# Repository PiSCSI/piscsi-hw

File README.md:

# piscsi-hw
Hardware Repository for PiSCSI

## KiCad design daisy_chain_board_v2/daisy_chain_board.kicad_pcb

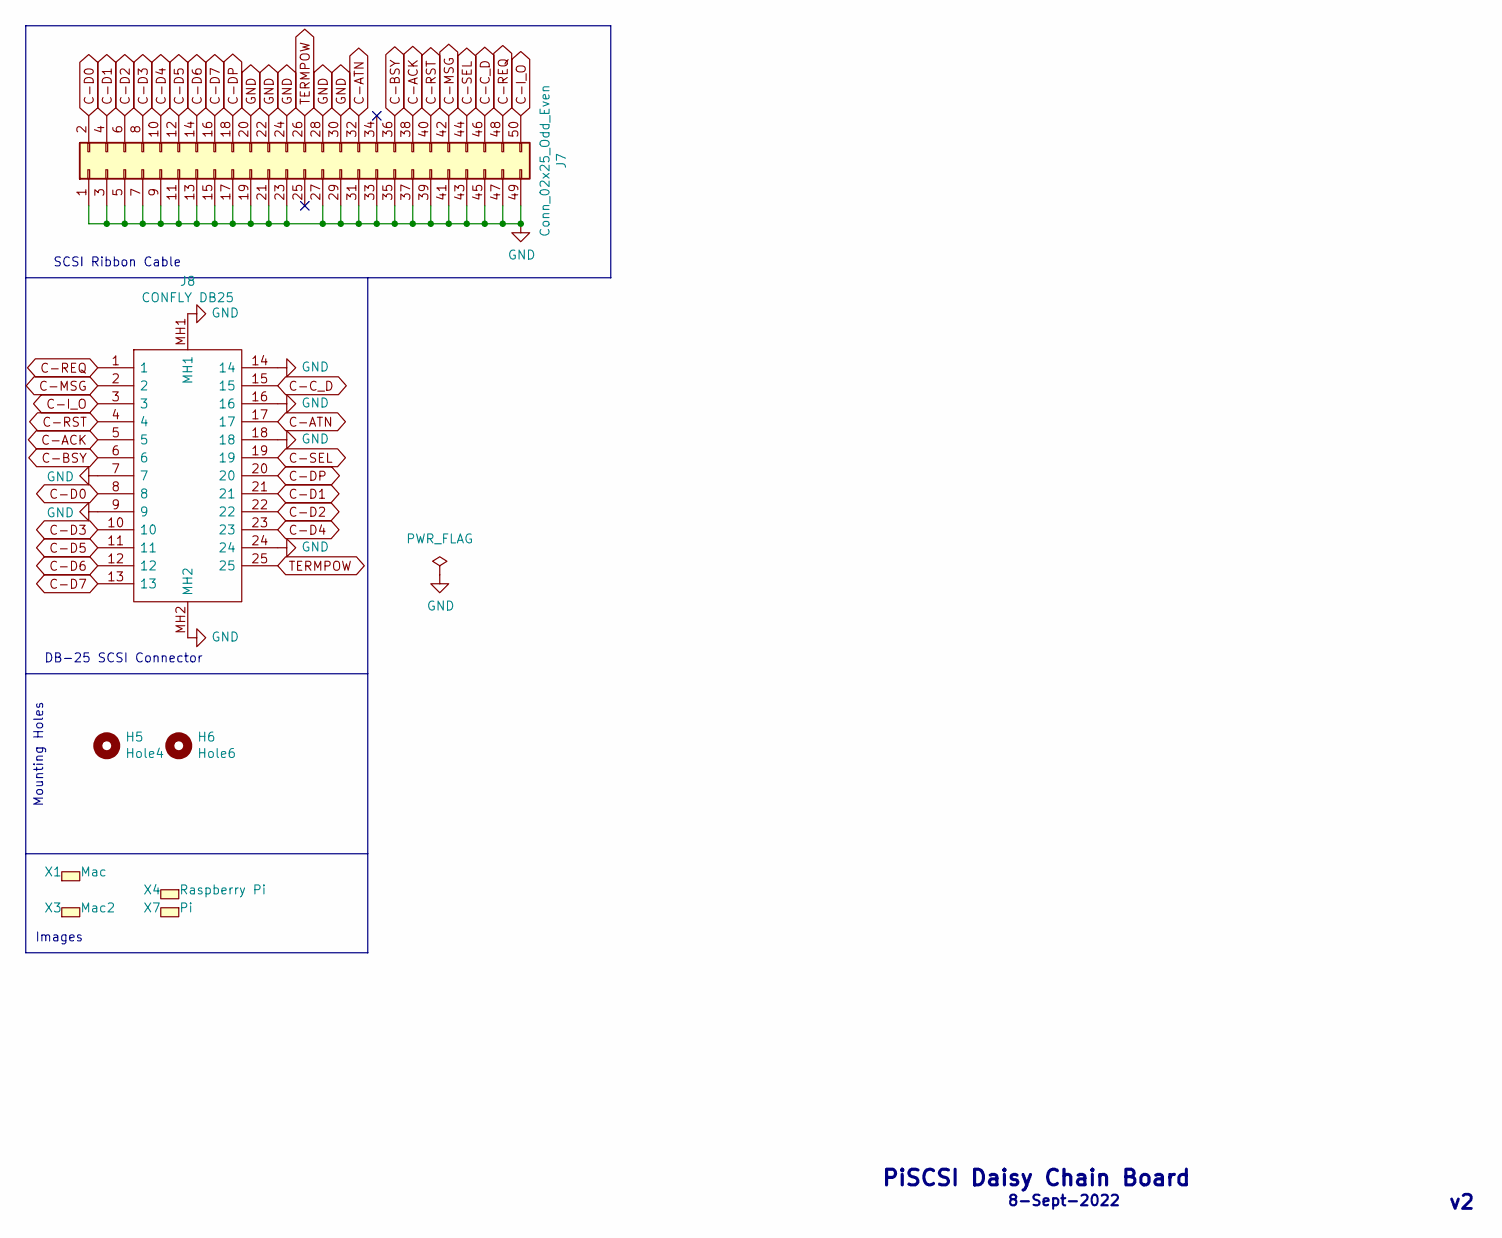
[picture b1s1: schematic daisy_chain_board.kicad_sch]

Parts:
H5: Hole4; MountingHole_2.7mm
H6: Hole6; MountingHole_2.7mm
J7: Conn_02x25_Odd_Even; PinHeader_2x25_P2.54mm_Vertical; LCSC C40024
J8: CONFLY DB25; L717SDB25PA4CH4F; Mouser Part Number 523-L717SDB25PA4CH4F
X1: Mac; mac_happy_small
X3: Mac2; mac_happy_small
X4: Raspberry Pi; pi_logo
X7: Pi; pi_logo

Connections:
C-ACK: J7.38, J8.5
C-ATN: J7.32, J8.17
C-BSY: J7.36, J8.6
C-C_D: J7.46, J8.15
C-D0: J7.2, J8.8
C-D1: J7.4, J8.21
C-D2: J7.6, J8.22
C-D3: J7.8, J8.10
C-D4: J7.10, J8.23
C-D5: J7.12, J8.11
C-D6: J7.14, J8.12
C-D7: J7.16, J8.13
C-DP: J7.18, J8.20
C-I_O: J7.50, J8.3
C-MSG: J7.42, J8.2
C-REQ: J7.48, J8.1
C-RST: J7.40, J8.4
C-SEL: J7.44, J8.19
GND: J7.1, J7.3, J7.5, J7.7, J7.9, J7.11, J7.13, J7.15, J7.17, J7.19, J7.20, J7.21, J7.22, J7.23, J7.24, J7.27, J7.28, J7.29, J7.30, J7.31, J7.33, J7.35, J7.37, J7.39, J7.41, J7.43, J7.45, J7.47, J7.49, J8.7, J8.9, J8.14, J8.16, J8.18, J8.24, J8.MH1, J8.MH2
TERMPOW: J7.26, J8.25

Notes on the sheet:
DB-25 SCSI Connector
Images
8-Sept-2022
PiSCSI Daisy Chain Board
Mounting Holes
SCSI Ribbon Cable

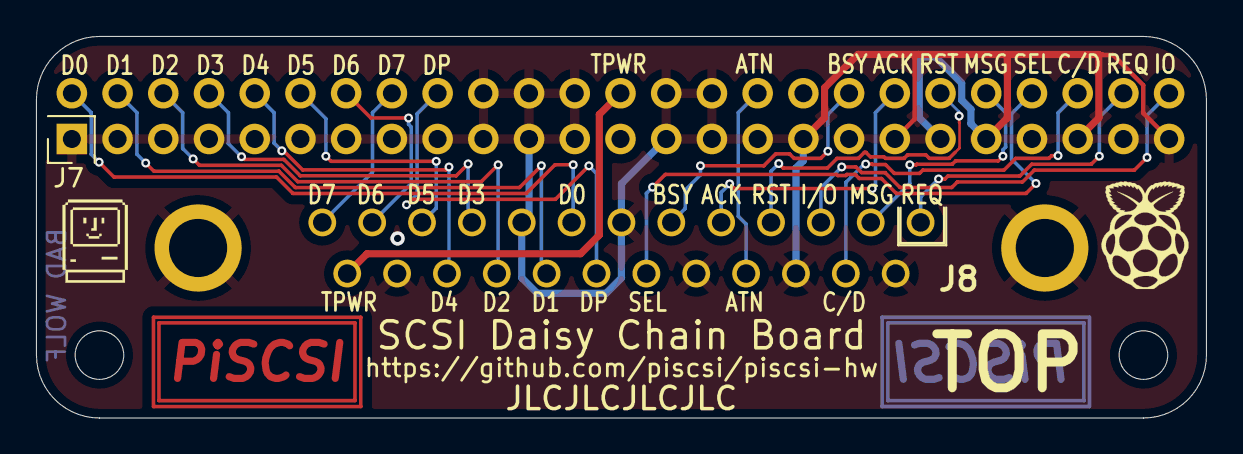
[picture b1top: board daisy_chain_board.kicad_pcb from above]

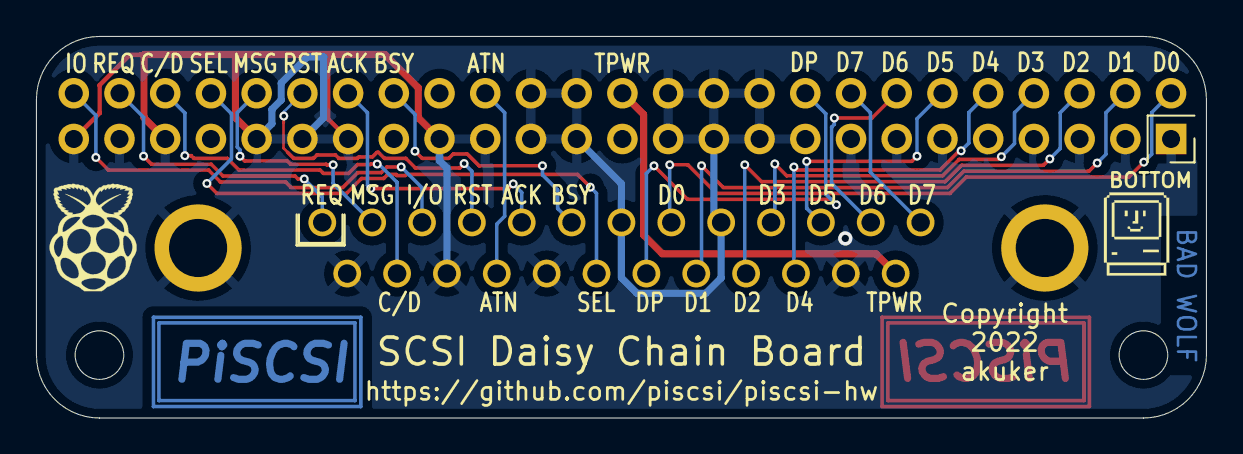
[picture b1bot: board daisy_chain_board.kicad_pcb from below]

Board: 2 copper layers, 65.0 x 21.2 mm, 8 parts (3 on the bottom side), 20 nets.

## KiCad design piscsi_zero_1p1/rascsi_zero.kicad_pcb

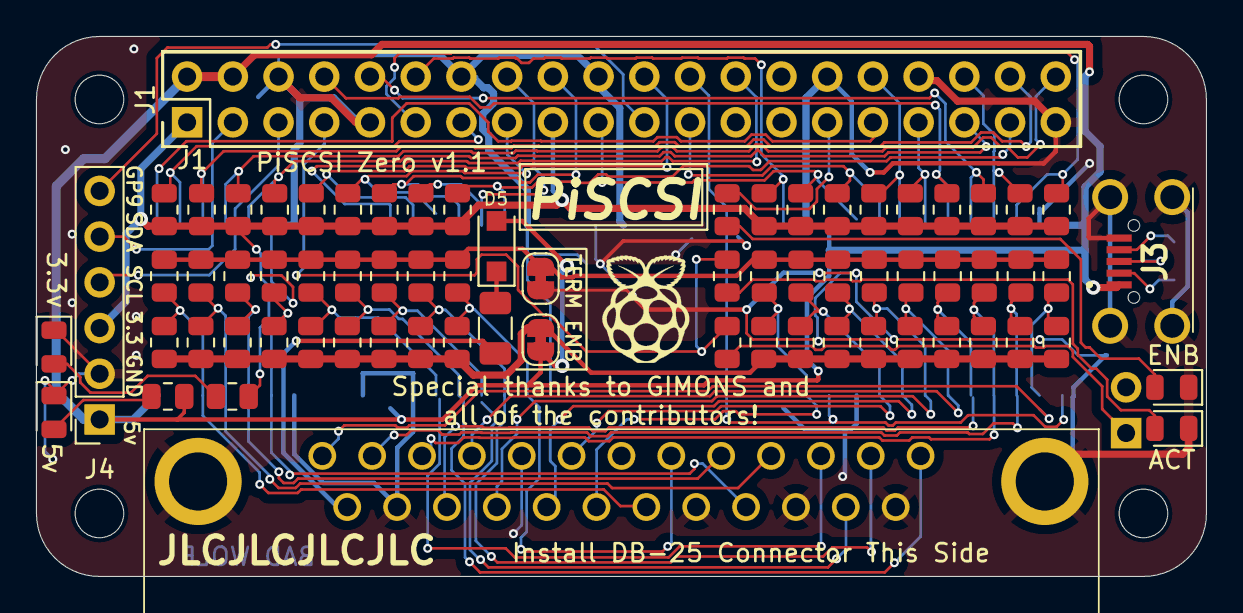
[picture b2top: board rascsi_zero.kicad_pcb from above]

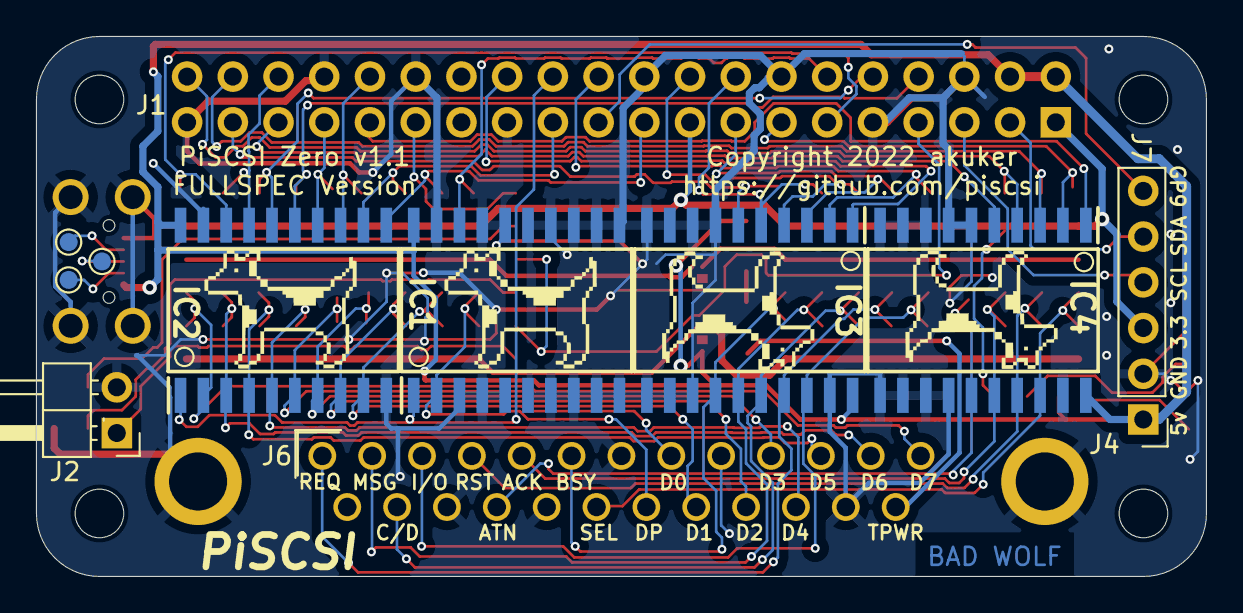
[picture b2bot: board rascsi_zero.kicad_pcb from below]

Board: 2 copper layers, 65.0 x 30.0 mm, 88 parts (13 on the bottom side), 59 nets.

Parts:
D1, D2, D3, D4: Green; LED_0805_2012Metric
D5: SM4007PL; D_SOD-123F
FUSE1: 1A; Fuse_1206_3216Metric
H1: Hole1; MountingHole_2.7mm_M2.5
H2: Hole2; MountingHole_2.7mm_M2.5
H3: Hole3; MountingHole_2.7mm_M2.5
H4: Hole5; MountingHole_2.7mm_M2.5
IC1, IC2, IC3, IC4: SN74LS641-1DW; SOIC127P1030X265-20N
J1: Raspberry_Pi_2_3; PinHeader_2x20_P2.54mm_Vertical
J2: DNP; PinHeader_1x02_P2.54mm_Horizontal
J3: U254-051N-4BH806; U254051N4BH806
J4: I2C Pinout; PinSocket_1x06_P2.54mm_Vertical
J6: CONNFLY DB-25; L717SDB25PA4CH4F
JP1, JP2: SolderJumper_2_Bridged; SolderJumper-2_P1.3mm_Bridged_RoundedPad1.0x1.5mm
R1, R2, R4: 2k; R_0805_2012Metric
R3: 5.1k; R_0805_2012Metric
R5, R6, R7, R8, R9, R10, R11, R12, R13, R14, R15, R16, R17, R18, R19, R20, R21, R22: 10k; R_0805_2012Metric
R23, R24, R25, R26, R27, R28, R29, R30, R31, R32, R33, R34, R35, R36, R37, R38, R39, R40: 220; R_0805_2012Metric
R41, R42, R43, R44, R45, R46, R47, R48, R49, R50, R51, R52, R53, R54, R55, R56, R57, R58: 330; R_0805_2012Metric
R59: 500; R_0805_2012Metric
TP1, TP2, TP3: TestPoint_Small; TestPoint_Pad_D1.0mm
X2, X4, X5, X6: Dogcow; dogcow
X7: Pi; pi_logo

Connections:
+3V3: J1.1 (3V3), J1.17 (3V3), J4.3, R4.1, R5.1, R6.1, R7.1, R8.1, R9.1, R10.1, R11.1, R12.1, R13.1, R14.1, R15.1, R16.1, R17.1, R18.1, R19.1, R20.1, R21.1, R22.1
+5V: D5.2 (A), IC1.20 (VCC), IC2.20 (VCC), IC3.20 (VCC), IC4.20 (VCC), J1.2 (5V), J1.4 (5V), J3.1, J4.1, JP1.2 (B), R3.1
/TERM_5v: JP1.1 (A), R23.1, R24.1, R25.1, R26.1, R27.1, R28.1, R29.1, R30.1, R31.1, R32.1, R33.1, R34.1, R35.1, R36.1, R37.1, R38.1, R39.1, R40.1
/TERM_GND: JP2.1 (A), R41.1, R42.1, R43.1, R44.1, R45.1, R46.1, R47.1, R48.1, R49.1, R50.1, R51.1, R52.1, R53.1, R54.1, R55.1, R56.1, R57.1, R58.1
C-ACK: IC4.16 (B3), J6.5, R24.2, R42.2
C-ATN: IC4.15 (B4), J6.17, R23.2, R41.2
C-BSY: IC3.14 (B5), J6.6, R27.2, R45.2
C-C_D: IC3.16 (B3), J6.15, R29.2, R47.2
C-D0: IC2.9 (A8), J6.8, R39.2, R57.2
C-D1: IC2.8 (A7), J6.21, R38.2, R56.2
C-D2: IC2.7 (A6), J6.22, R37.2, R55.2
C-D3: IC2.6 (A5), J6.10, R36.2, R54.2
C-D4: IC2.5 (A4), J6.23, R35.2, R53.2
C-D5: IC2.4 (A3), J6.11, R34.2, R52.2
C-D6: IC2.3 (A2), J6.12, R33.2, R51.2
C-D7: IC2.2 (A1), J6.13, R32.2, R50.2
C-DP: IC1.2 (A1), J6.20, R40.2, R58.2
C-I_O: IC3.18 (B1), J6.3, R31.2, R49.2
C-MSG: IC3.15 (B4), J6.2, R28.2, R46.2
C-REQ: IC3.17 (B2), J6.1, R30.2, R48.2
C-RST: IC4.17 (B2), J6.4, R25.2, R43.2
C-SEL: IC4.18 (B1), J6.19, R26.2, R44.2
DBG_LED: J1.29 (GCLK1/GPIO5), R2.1
EXT-ACT-LED: J2.1, R59.2
GND: D1.1 (K), D2.1 (K), D3.1 (K), D4.1 (K), IC1.3 (A2), IC1.4 (A3), IC1.5 (A4), IC1.6 (A5), IC1.7 (A6), IC1.8 (A7), IC1.9 (A8), IC1.10 (GND), IC1.11 (B8), IC1.12 (B7), IC1.13 (B6), IC1.14 (B5), IC1.15 (B4), IC1.16 (B3), IC1.17 (B2), IC1.19 (~OE), IC2.10 (GND), IC2.19 (~OE), IC3.7 (A6), IC3.8 (A7), IC3.9 (A8), IC3.10 (GND), IC3.11 (B8), IC3.12 (B7), IC3.13 (B6), IC3.19 (~OE), IC4.6 (A5), IC4.7 (A6), IC4.8 (A7), IC4.9 (A8), IC4.10 (GND), IC4.11 (B8), IC4.12 (B7), IC4.13 (B6), IC4.14 (B5), IC4.19 (~OE), J1.6 (GND), J1.9 (GND), J1.14 (GND), J1.20 (GND), J1.25 (GND), J1.30 (GND), J1.34 (GND), J1.39 (GND), J2.2, J3.5, J3.MH1, J3.MH2, J3.MH3, J3.MH4, J4.2, J6.7, J6.9, J6.14, J6.16, J6.18, J6.24, J6.MH1, J6.MH2, JP2.2 (B)
unnamed: D1.2 (A), R1.2
unnamed: D2.2 (A), R2.2
unnamed: D3.2 (A), R3.2
unnamed: D4.2 (A), R4.2
unnamed: D5.1 (K), FUSE1.1
unnamed: J3.2, TP1.1
unnamed: J3.3, TP2.1
unnamed: J3.4, TP3.1
PI-ACK: IC4.4 (A3), J1.40 (GPIO21/SCLK1), R6.2
PI-ACT: J1.7 (GCLK0/GPIO4), R1.1, R59.1
PI-ATN: IC4.5 (A4), J1.35 (GPIO19/MISO1), R5.2
PI-BSY: IC3.6 (A5), J1.37 (GPIO26), R9.2
PI-C_D: IC3.4 (A3), J1.18 (GPIO24), R11.2
PI-D0: IC2.11 (B8), J1.19 (MOSI0/GPIO10), R21.2
PI-D1: IC2.12 (B7), J1.23 (SCLK0/GPIO11), R20.2
PI-D2: IC2.13 (B6), J1.32 (PWM0/GPIO12), R19.2
PI-D3: IC2.14 (B5), J1.33 (PWM1/GPIO13), R18.2
PI-D4: IC2.15 (B4), J1.8 (GPIO14/TXD), R17.2
PI-D5: IC2.16 (B3), J1.10 (GPIO15/RXD), R16.2
PI-D6: IC2.17 (B2), J1.36 (GPIO16), R15.2
PI-D7: IC2.18 (B1), J1.11 (GPIO17), R14.2
PI-DP: IC1.18 (B1), J1.12 (GPIO18/PWM0), R22.2
PI-DTD: IC1.1 (DIR), IC2.1 (DIR), J1.24 (~CE0/GPIO8)
PI-GPIO9: J1.21 (MISO0/GPIO9), J4.6
PI-IND: IC4.1 (DIR), J1.31 (GCLK2/GPIO6)
PI-I_O: IC3.2 (A1), J1.22 (GPIO25), R13.2
PI-MSG: IC3.5 (A4), J1.16 (GPIO23), R10.2
PI-REQ: IC3.3 (A2), J1.15 (GPIO22), R12.2
PI-RST: IC4.3 (A2), J1.38 (GPIO20/MOSI1), R7.2
PI-SEL: IC4.2 (A1), J1.13 (GPIO27), R8.2
PI-TAD: IC3.1 (DIR), J1.26 (~CE1/GPIO7)
PI_SCL: J1.5 (SCL/GPIO3), J4.4
PI_SDA: J1.3 (SDA/GPIO2), J4.5
TERMPOW: FUSE1.2, J6.25

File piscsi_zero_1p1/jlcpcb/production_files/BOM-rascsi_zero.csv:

Comment,Designator,Footprint,LCSC
Raspberry_Pi_2_3,J1,PinHeader_2x20_P2.54mm_Vertical,C124383
SN74LS641-1DW,"IC1,IC2,IC3,IC4",SOIC127P1030X265-20N,C1548111
500,R59,R_0805_2012Metric,C17408
10k,"R10,R11,R12,R13,R14,R15,R16,R17,R18,R19,R20,R21,R22,R5,R6,R7,R8,R9",R_0805_2012Metric,C17414
220,"R23,R24,R25,R26,R27,R28,R29,R30,R31,R32,R33,R34,R35,R36,R37,R38,R39,R40",R_0805_2012Metric,C17557
2k,"R1,R2,R4",R_0805_2012Metric,C17604
330,"R41,R42,R43,R44,R45,R46,R47,R48,R49,R50,R51,R52,R53,R54,R55,R56,R57,R58",R_0805_2012Metric,C17630
1A,FUSE1,Fuse_1206_3216Metric,C182974
Green,"D1,D2,D3,D4",LED_0805_2012Metric,C2297
5.1k,R3,R_0805_2012Metric,C27834
U254-051N-4BH806,J3,U254051N4BH806,C319170
DNP,J2,PinHeader_1x02_P2.54mm_Horizontal,C376120
I2C Pinout,J4,PinSocket_1x06_P2.54mm_Vertical,C50950
SM4007PL,D5,D_SOD-123F,C64898
CONNFLY DB-25,J6,L717SDB25PA4CH4F,C77838
Hole1,H1,MountingHole_2.7mm_M2.5,
Hole3,H3,MountingHole_2.7mm_M2.5,
Hole5,H4,MountingHole_2.7mm_M2.5,
Hole2,H2,MountingHole_2.7mm_M2.5,
Pi,X7,pi_logo,
SolderJumper_2_Bridged,JP1,SolderJumper-2_P1.3mm_Bridged_RoundedPad1.0x1.5mm,
SolderJumper_2_Bridged,JP2,SolderJumper-2_P1.3mm_Bridged_RoundedPad1.0x1.5mm,
TestPoint_Small,TP1,TestPoint_Pad_D1.0mm,
TestPoint_Small,TP2,TestPoint_Pad_D1.0mm,
TestPoint_Small,TP3,TestPoint_Pad_D1.0mm,

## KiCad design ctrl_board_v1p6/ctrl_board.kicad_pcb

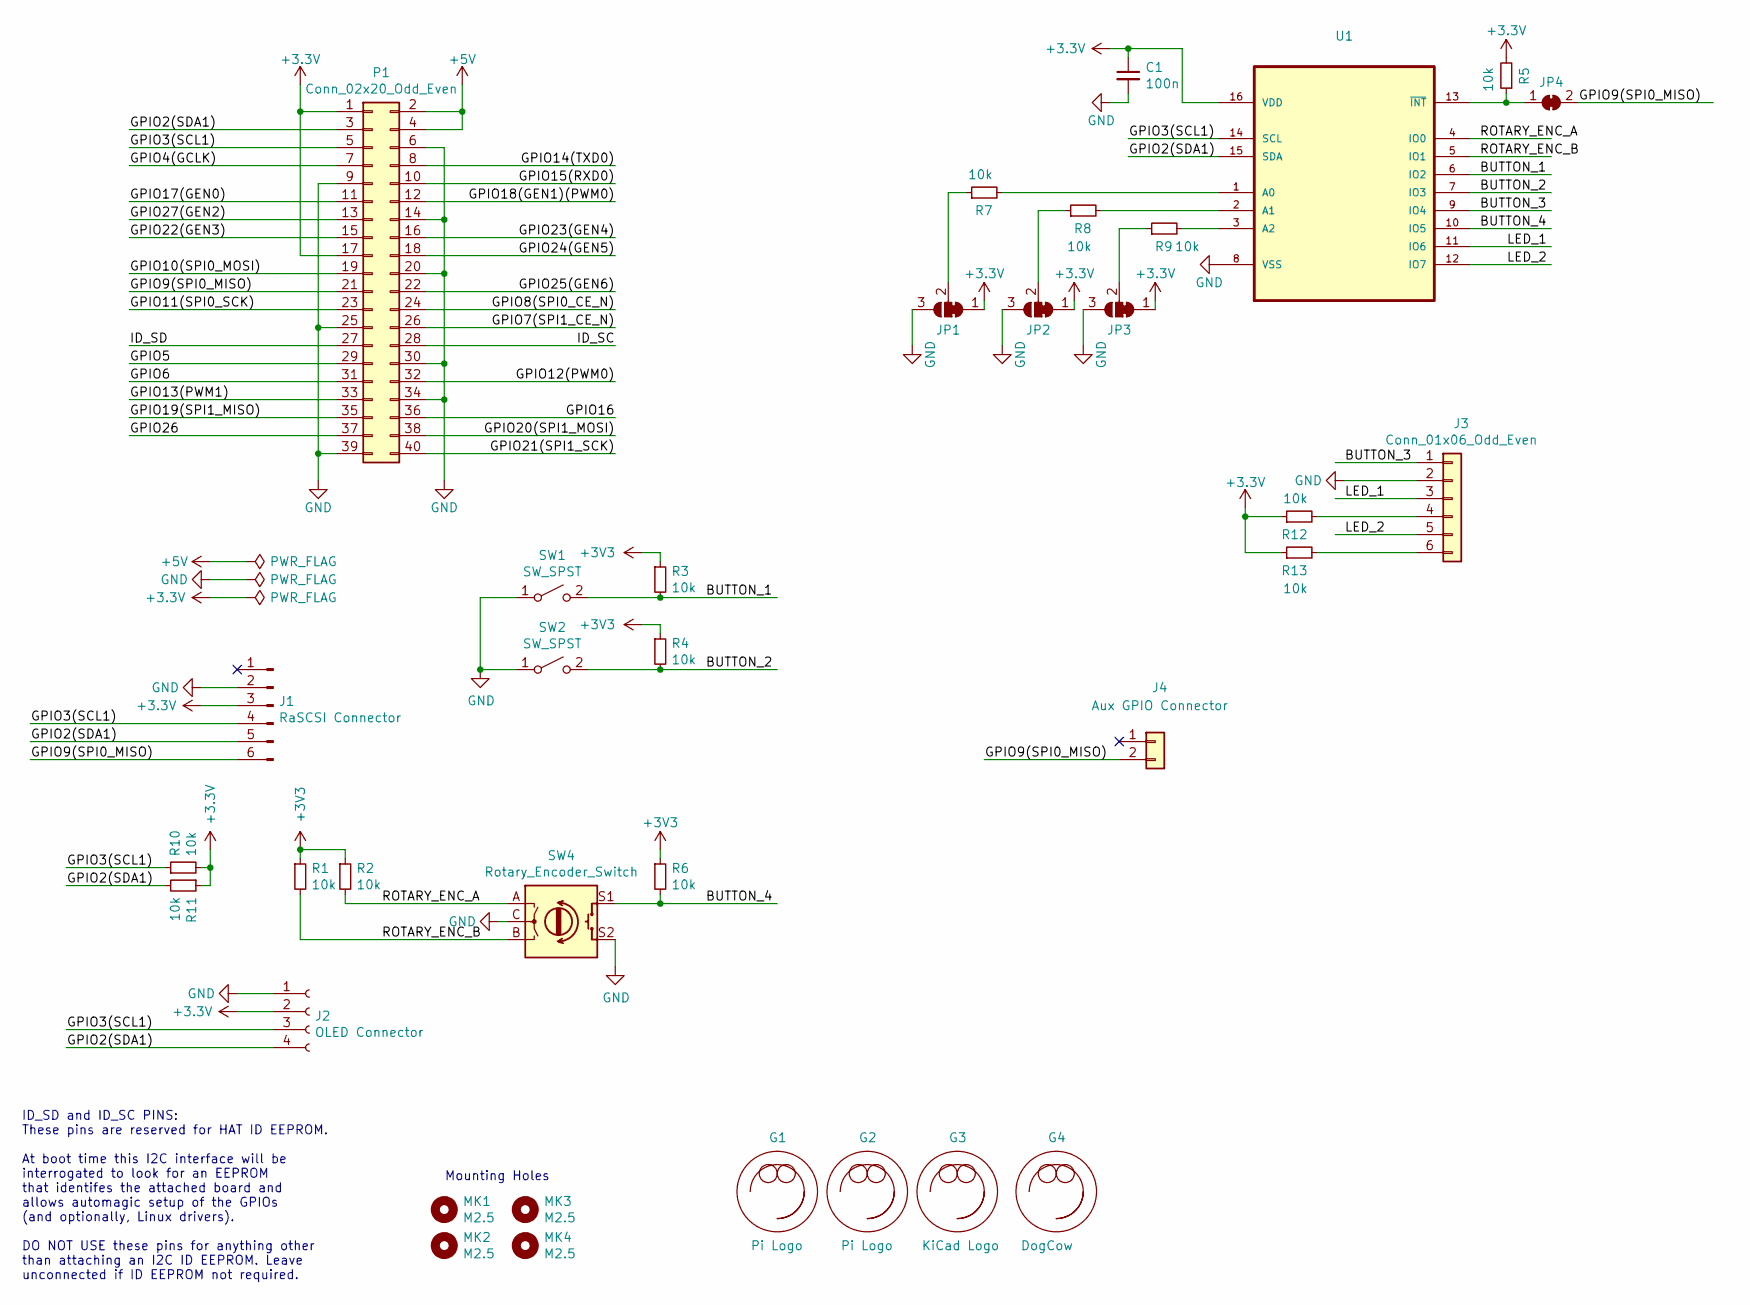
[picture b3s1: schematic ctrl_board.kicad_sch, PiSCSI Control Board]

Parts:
C1: 100n; C_0805_2012Metric; LCSC C49678
G1, G2: Pi Logo; pi_logo
G3: KiCad Logo; KiCad-Logo2_5mm_SilkScreen
G4: DogCow; dogcow
J1: RaSCSI Connector; PinHeader_1x06_P2.54mm_Vertical
J2: OLED Connector; 0.9_and_1.3_in_OLED_Footprint
J3: Conn_01x06_Odd_Even; PinHeader_1x06_P2.54mm_Vertical
J4: Aux GPIO Connector; PinHeader_1x02_P2.54mm_Vertical
JP1, JP2, JP3: SolderJumper_3_Bridged12; SolderJumper-3_P1.3mm_Bridged12_RoundedPad1.0x1.5mm
JP4: SolderJumper_2_Open; SolderJumper-2_P1.3mm_Bridged_RoundedPad1.0x1.5mm
MK1, MK2, MK3, MK4: M2.5; MountingHole_2.7mm_M2.5
P1: Conn_02x20_Odd_Even; PinSocket_2x20_P2.54mm_Vertical
R1, R2, R3, R4, R5, R6, R7, R8, R9, R10, R11, R12, R13: 10k; R_0805_2012Metric; LCSC C17414
SW1, SW2: SW_SPST; SW_PUSH_6mm_H5mm; LCSC C110153
SW4: Rotary_Encoder_Switch; RotaryEncoder_Alps_EC11E-Switch_Vertical_H20mm
U1: MPN PCA9554APW,118; LCSC C86803

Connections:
+5V: P1.2, P1.4
/BUTTON_1: R3.2, SW1.2 (B), U1.6 (IO2)
/BUTTON_2: R4.2, SW2.2 (B), U1.7 (IO3)
/BUTTON_3: J3.1, U1.9 (IO4)
/BUTTON_4: R6.2, SW4.S1, U1.10 (IO5)
/GPIO2(SDA1): J1.5, J2.4, P1.3, R11.2, U1.15 (SDA)
/GPIO3(SCL1): J1.4, J2.3, P1.5, R10.1, U1.14 (SCL)
/GPIO4(GCLK): P1.7
/GPIO5: P1.29
/GPIO6: P1.31
/GPIO7(SPI1_CE_N): P1.26
/GPIO8(SPI0_CE_N): P1.24
/GPIO9(SPI0_MISO): J1.6, J4.2, JP4.2 (B), P1.21
/GPIO10(SPI0_MOSI): P1.19
/GPIO11(SPI0_SCK): P1.23
/GPIO12(PWM0): P1.32
/GPIO13(PWM1): P1.33
/GPIO14(TXD0): P1.8
/GPIO15(RXD0): P1.10
/GPIO16: P1.36
/GPIO17(GEN0): P1.11
/GPIO18(GEN1)(PWM0): P1.12
/GPIO19(SPI1_MISO): P1.35
/GPIO20(SPI1_MOSI): P1.38
/GPIO21(SPI1_SCK): P1.40
/GPIO22(GEN3): P1.15
/GPIO23(GEN4): P1.16
/GPIO24(GEN5): P1.18
/GPIO25(GEN6): P1.22
/GPIO26: P1.37
/GPIO27(GEN2): P1.13
/ID_SC: P1.28
/ID_SD: P1.27
/LED_1: J3.3, U1.11 (IO6)
/LED_2: J3.5, U1.12 (IO7)
/ROTARY_ENC_A: R2.2, SW4.A, U1.4 (IO0)
/ROTARY_ENC_B: R1.2, SW4.B, U1.5 (IO1)
GND: C1.2, J1.2, J2.1, J3.2, JP1.3 (B), JP2.3 (B), JP3.3 (B), P1.6, P1.9, P1.14, P1.20, P1.25, P1.30, P1.34, P1.39, SW1.1 (A), SW2.1 (A), SW4.C, SW4.S2, U1.8 (VSS)
unnamed: J3.4, R12.2
unnamed: J3.6, R13.2
unnamed: JP1.2 (C), R7.1
unnamed: JP2.2 (C), R8.1
unnamed: JP3.2 (C), R9.1
unnamed: JP4.1 (A), R5.1, U1.13 (~INT)
unnamed: R7.2, U1.1 (A0)
unnamed: R8.2, U1.2 (A1)
unnamed: R9.2, U1.3 (A2)

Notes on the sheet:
ID_SD and ID_SC PINS: These pins are reserved for HAT ID EEPROM. At boot time this I2C interface will be interrogated to look for an EEPROM that identifes the attached board and allows automagic setup of the GPIOs (and optionally, Linux drivers). DO NOT USE these pins for anything other than attach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
Mounting Holes

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
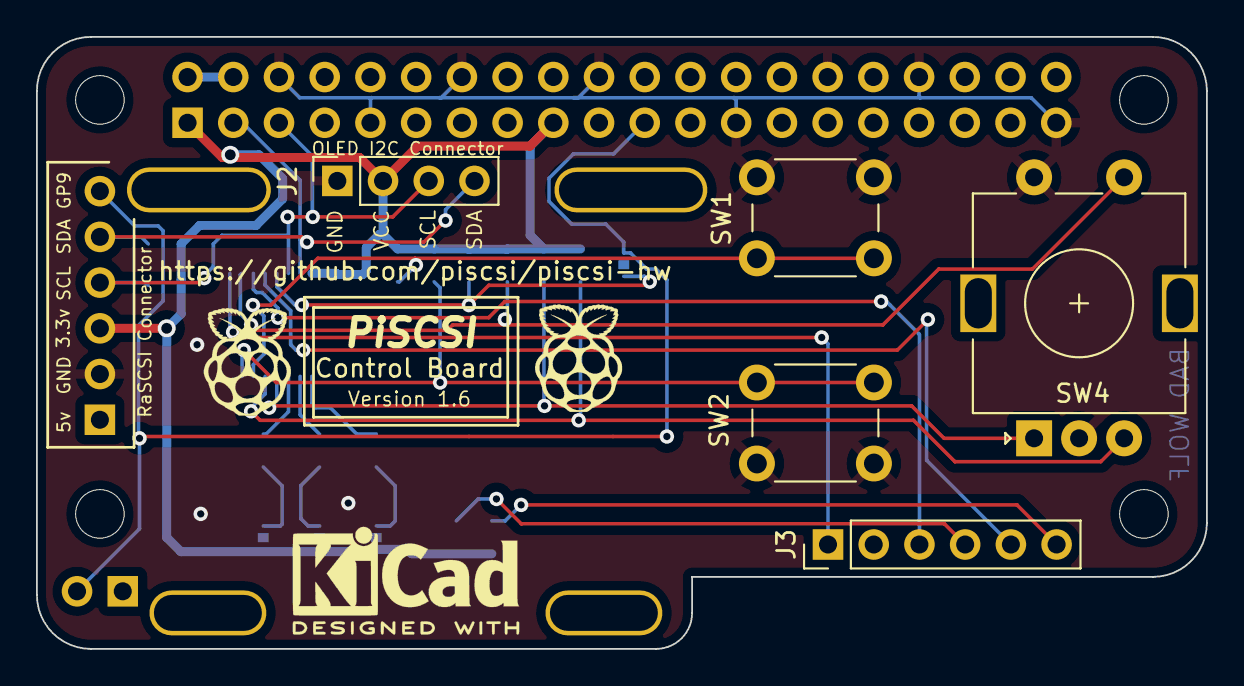
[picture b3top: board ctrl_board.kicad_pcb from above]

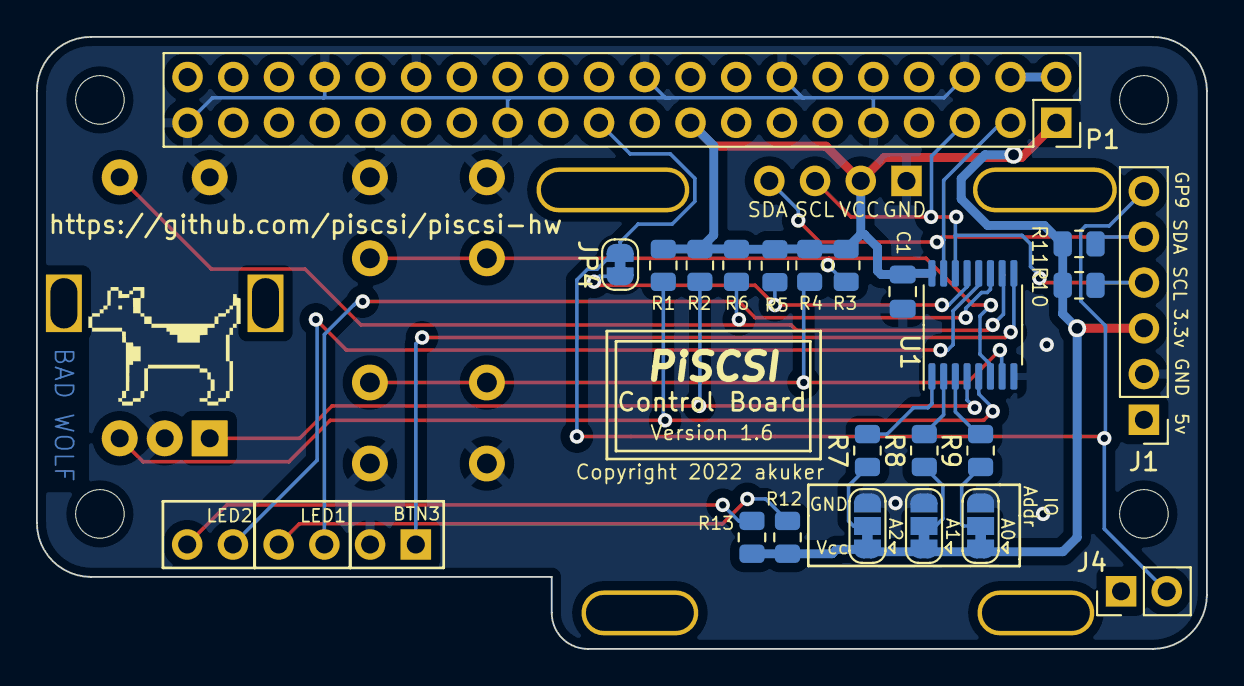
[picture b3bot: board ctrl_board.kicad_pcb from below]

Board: 2 copper layers, 65.0 x 34.0 mm, 35 parts (26 on the bottom side), 23 nets.

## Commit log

2020-07-10 Commit version 1.5 of the RASCSI board from https://github.com/akuker/RASCSI-68kmlaver
2020-07-10 Opened with KiCad to fix file/library errors
2020-07-10 Commit version 1.5 schematic
2020-08-01 First draft of rascsi version 2.1
2020-08-01 Generated gerber files, part lists and re-generated schematic
2020-08-02 Fixed silkscreen for tranceivers
2020-08-03 Fixed orientation of termpwr diode. Updated to version "2.1a"
2020-08-03 Regenerated BOM, footprint listing, GERBER files and Schematic
2020-08-03 Changed Bus Transceivers to 74LS641-1 per discussion on 68kmla forums
2020-08-08 Generate bill of materials for version 1.5
2020-08-14 Created version 1.6 with issue #10 fixed. Renamed version 1.5 to a better folder name
2020-08-23 Version 2.2 of the fullspec board with surface mount parts (#24)
    * Version 2.2 of the fullspec board with surface mount parts
    * Create testing device for rascsi hardware
    * Updated daisychain board to include the TERMPWR signal
2020-09-12 Proposed 2p3 version - Added RPi HAT EEPROM, fixed 3v/5v LED caption, added copper to USB port traces
2020-09-22 Commit ordered version of the board
2020-09-22 Updated to correct part fields and descriptions. Removed conflicting mouser references
2020-10-17 Create IIciCase.FCStd (#44)
2021-01-19 Generated .STEP file for RaSCSI
2021-01-22 Added STEP file and updated symbol and 3d model references to reference the correct gender of parts. Should be no functional change
2021-01-22 Added 3D models and correct footprints for STEP file
2021-05-22 Added loopback schematic
2021-05-22 Remove schematic
2021-06-08 RaSCSI hardware version 2.4 (#94)
    * First attempt at adding 2.5 inch drive connector
    * Clean up silkscreen and fix DRC issues
    * additional cleanup. Made Pin 1 of the PB connector square
    * minor tweaks
    * Updates for ordered version
    * Generate step file and schematic pdf
2021-06-09 Merge Hw 2p4 to develop (#109)
    * First attempt at adding 2.5 inch drive connector
    * Clean up silkscreen and fix DRC issues
    * additional cleanup. Made Pin 1 of the PB connector square
    * minor tweaks
    * Updates for ordered version
    * Generated .STEP file for RaSCSI
2021-11-14 Fix daisychain board files (#462)
    * Revert "Added STEP file and updated symbol and 3d model references to reference the correct gender of parts. Should be no functional change"
    This reverts commit 479cc578b885d9d675a35aab40d5217a447c2dfc.
    * Delete rascsi_tester that didn't work
2021-12-20 RaSCSI Zero version 1.0 (#546)
2021-12-20 Loopback tester pcb (#545)
2022-01-17 Generate PDF of schematic (#615)
2022-03-03 Hardware Version 2.5 (#720)
    * Added header for external ENB LED
    * test fixture for rascsi
    * test fixture for rascsi
    * Updated to Kicad 6 and modified act LED
    * Regenerated Gerber files to fix drill placement. Added CE logo
    * Regeneraged gerbers
2022-03-03 Control board for managing the RaSCSI configuration (#721)
    * First draft of control board - Issue #382
    * routed signals
    * Fixed up silkscreens and added mousebites
    * Fixed up silkscreens and added mousebites
    * 3d models of encoder and display
    * cleaned up layout
2022-03-14 Added Schematic PDF file and Step 3D model (#726)
    * Add PDF of schematic and step file
    * ignore kicad backups
    * Moved PDF files to the RASCSI.wiki repo
2022-11-30 Create CODEOWNERS
2022-11-30 Update CODEOWNERS
2022-12-12 rascsi 2p6 and daisy chain rebrand
2022-12-14 updated control board and updated text on daisy chain board
2023-01-21 update silkscreen to say piscsi and regenerate prod files
2023-01-21 add prod files
2023-01-21 remove temp file
2023-01-21 add macos hidden files and remove csv
2023-01-22 rebrand
2023-01-22 Revert back to original version of rascsi 2.6 board.
    This reverts commit 2b424468fa236e169660193e1614c490b0ff0ed6.
2023-01-22 ignore macos temp file
2023-01-22 ignore backup dirs
2023-01-22 remove extra files
2023-01-29 rename to 2.7
2023-01-30 as ordered 2.7
2023-02-25 Piscsi 2p7 (#3)
2023-02-25 Update 2.6 board with new branding silkscreen. No functional updates (#2)
2023-02-25 updated control board and updated text on daisy chain board (#4)
2023-02-27 PiSCSI Zero 1.1 files
2023-02-27 PiSCSI Zero 1.1 files (#5)
2023-03-15 Update LICENSE
2023-03-15 rebranded to piscsi
2023-03-15 Piscsi 2p7 and daisy chain v2 (#6)
    * rebrand
    * rebrand
    * ignore macos temp file
    * rename to 2.7
    * as ordered 2.7
    * rebranded to piscsi
2023-05-01 regenerate schematic and convert to KiCad 7
2023-05-01 Updated to Kicad 7 & regenerate schematic
2024-04-04 regenerated piscsi zero prod files
2024-04-04 regenerated production files

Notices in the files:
ctrl_board_v1p6/ctrl_board.kicad_pcb:
Copyright 2022 akuker
